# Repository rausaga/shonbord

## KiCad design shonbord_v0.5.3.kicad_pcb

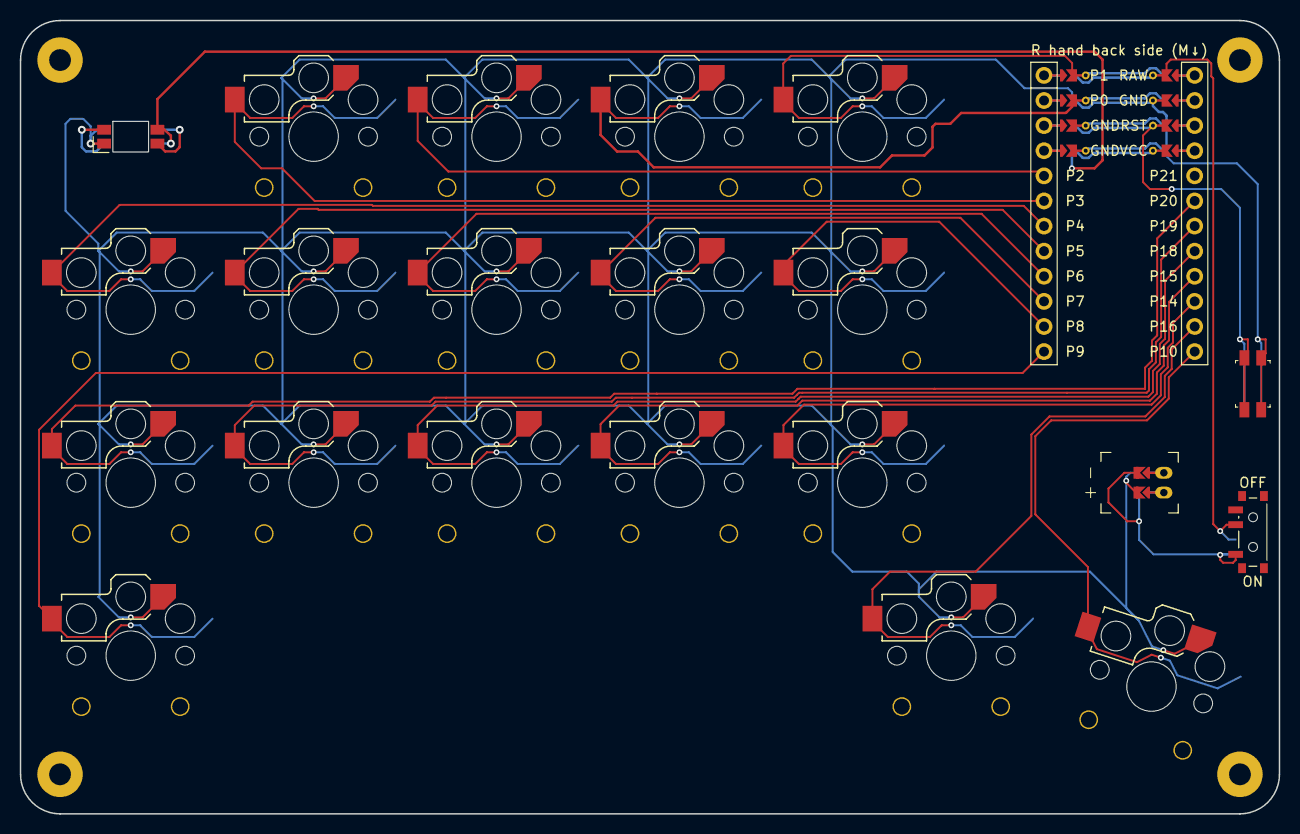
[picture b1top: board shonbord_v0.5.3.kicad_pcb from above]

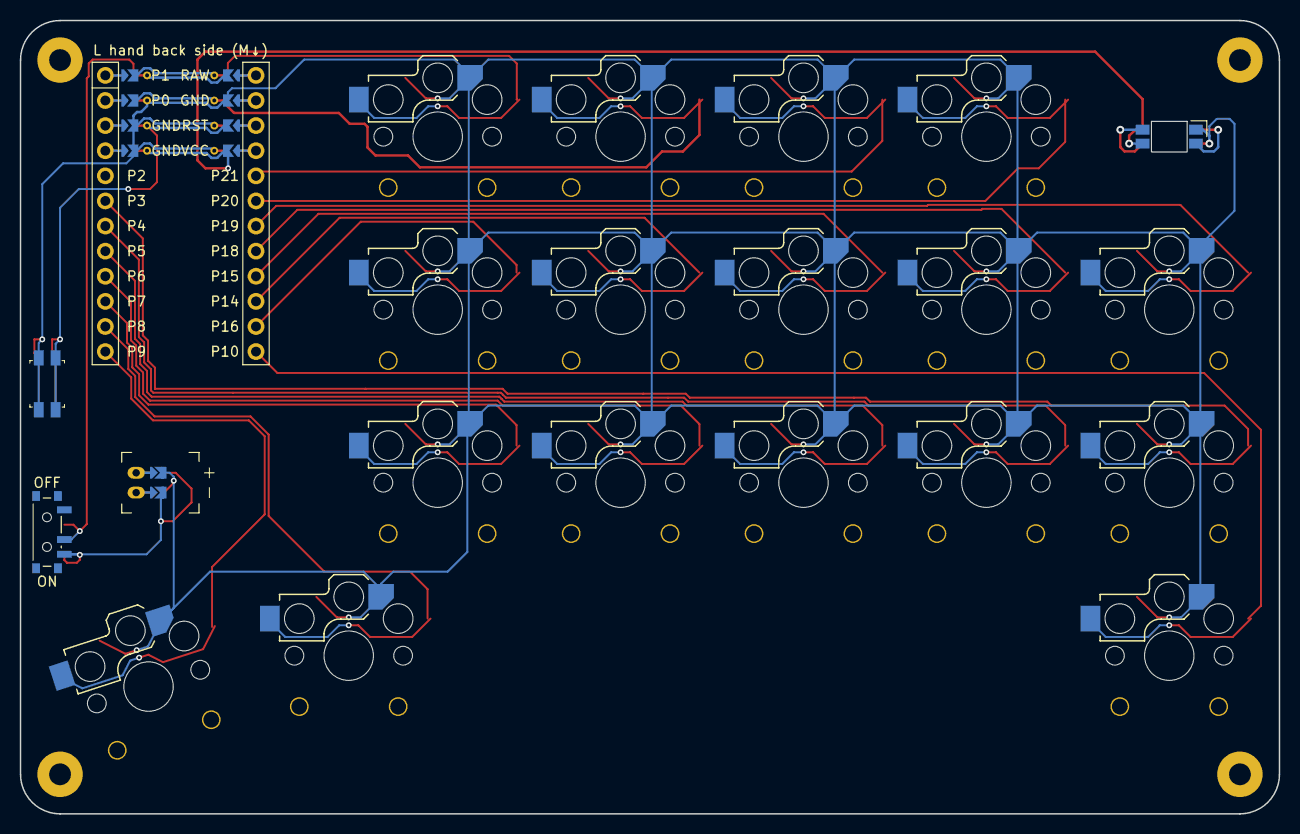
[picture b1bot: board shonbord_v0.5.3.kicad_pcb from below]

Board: 2 copper layers, 127.3 x 80.2 mm, 26 parts (18 on the bottom side), 24 nets.

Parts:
JST1: battery_connector_jst_ph_2
LED1: led_SK6812mini-e (per-key, reversible)
MCU1: mcu_nice_nano
MH1, MH2, MH3, MH4: mounting_hole_npth
PWR1: power_switch_smd_side
RST1: reset_switch_smd_side
S1, S2, S3, S4, S5, S6, S7, S8, S9, S10, S11, S12, S13, S14, S15, S16, S17: switch_choc_v1_v2

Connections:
BAT_P: JST1.1, PWR1.1, PWR1.3
GND: JST1.2, LED1.3, MCU1.102, MCU1.121, MCU1.122, RST1.1, RST1.3, S1.1, S2.1, S3.1, S4.1, S5.1, S6.1, S7.1, S8.1, S9.1, S10.1, S11.1, S12.1, S13.1, S14.1, S15.1, S16.1, S17.1
JST1_1: JST1.11, JST1.21, JST1.31
JST1_2: JST1.12, JST1.22, JST1.32
P0: MCU1.123, S12.2
P1: MCU1.124, S15.2
P2: MCU1.20, S9.2
P3: MCU1.19, S6.2
P4: MCU1.18, S3.2
P5: MCU1.17, S5.2
P6: MCU1.16, S8.2
P7: MCU1.15, S11.2
P8: MCU1.14, S14.2
P9: MCU1.13, S1.2
P10: MCU1.12, S17.2
P14: MCU1.10, S13.2
P15: MCU1.9, S10.2
P16: MCU1.11, S16.2
P18: MCU1.8, S7.2
P19: MCU1.7, S4.2
P20: MCU1.6, S2.2
RAW: MCU1.101, PWR1.2
RST: MCU1.103, RST1.2, RST1.4
VCC: LED1.1, MCU1.104
